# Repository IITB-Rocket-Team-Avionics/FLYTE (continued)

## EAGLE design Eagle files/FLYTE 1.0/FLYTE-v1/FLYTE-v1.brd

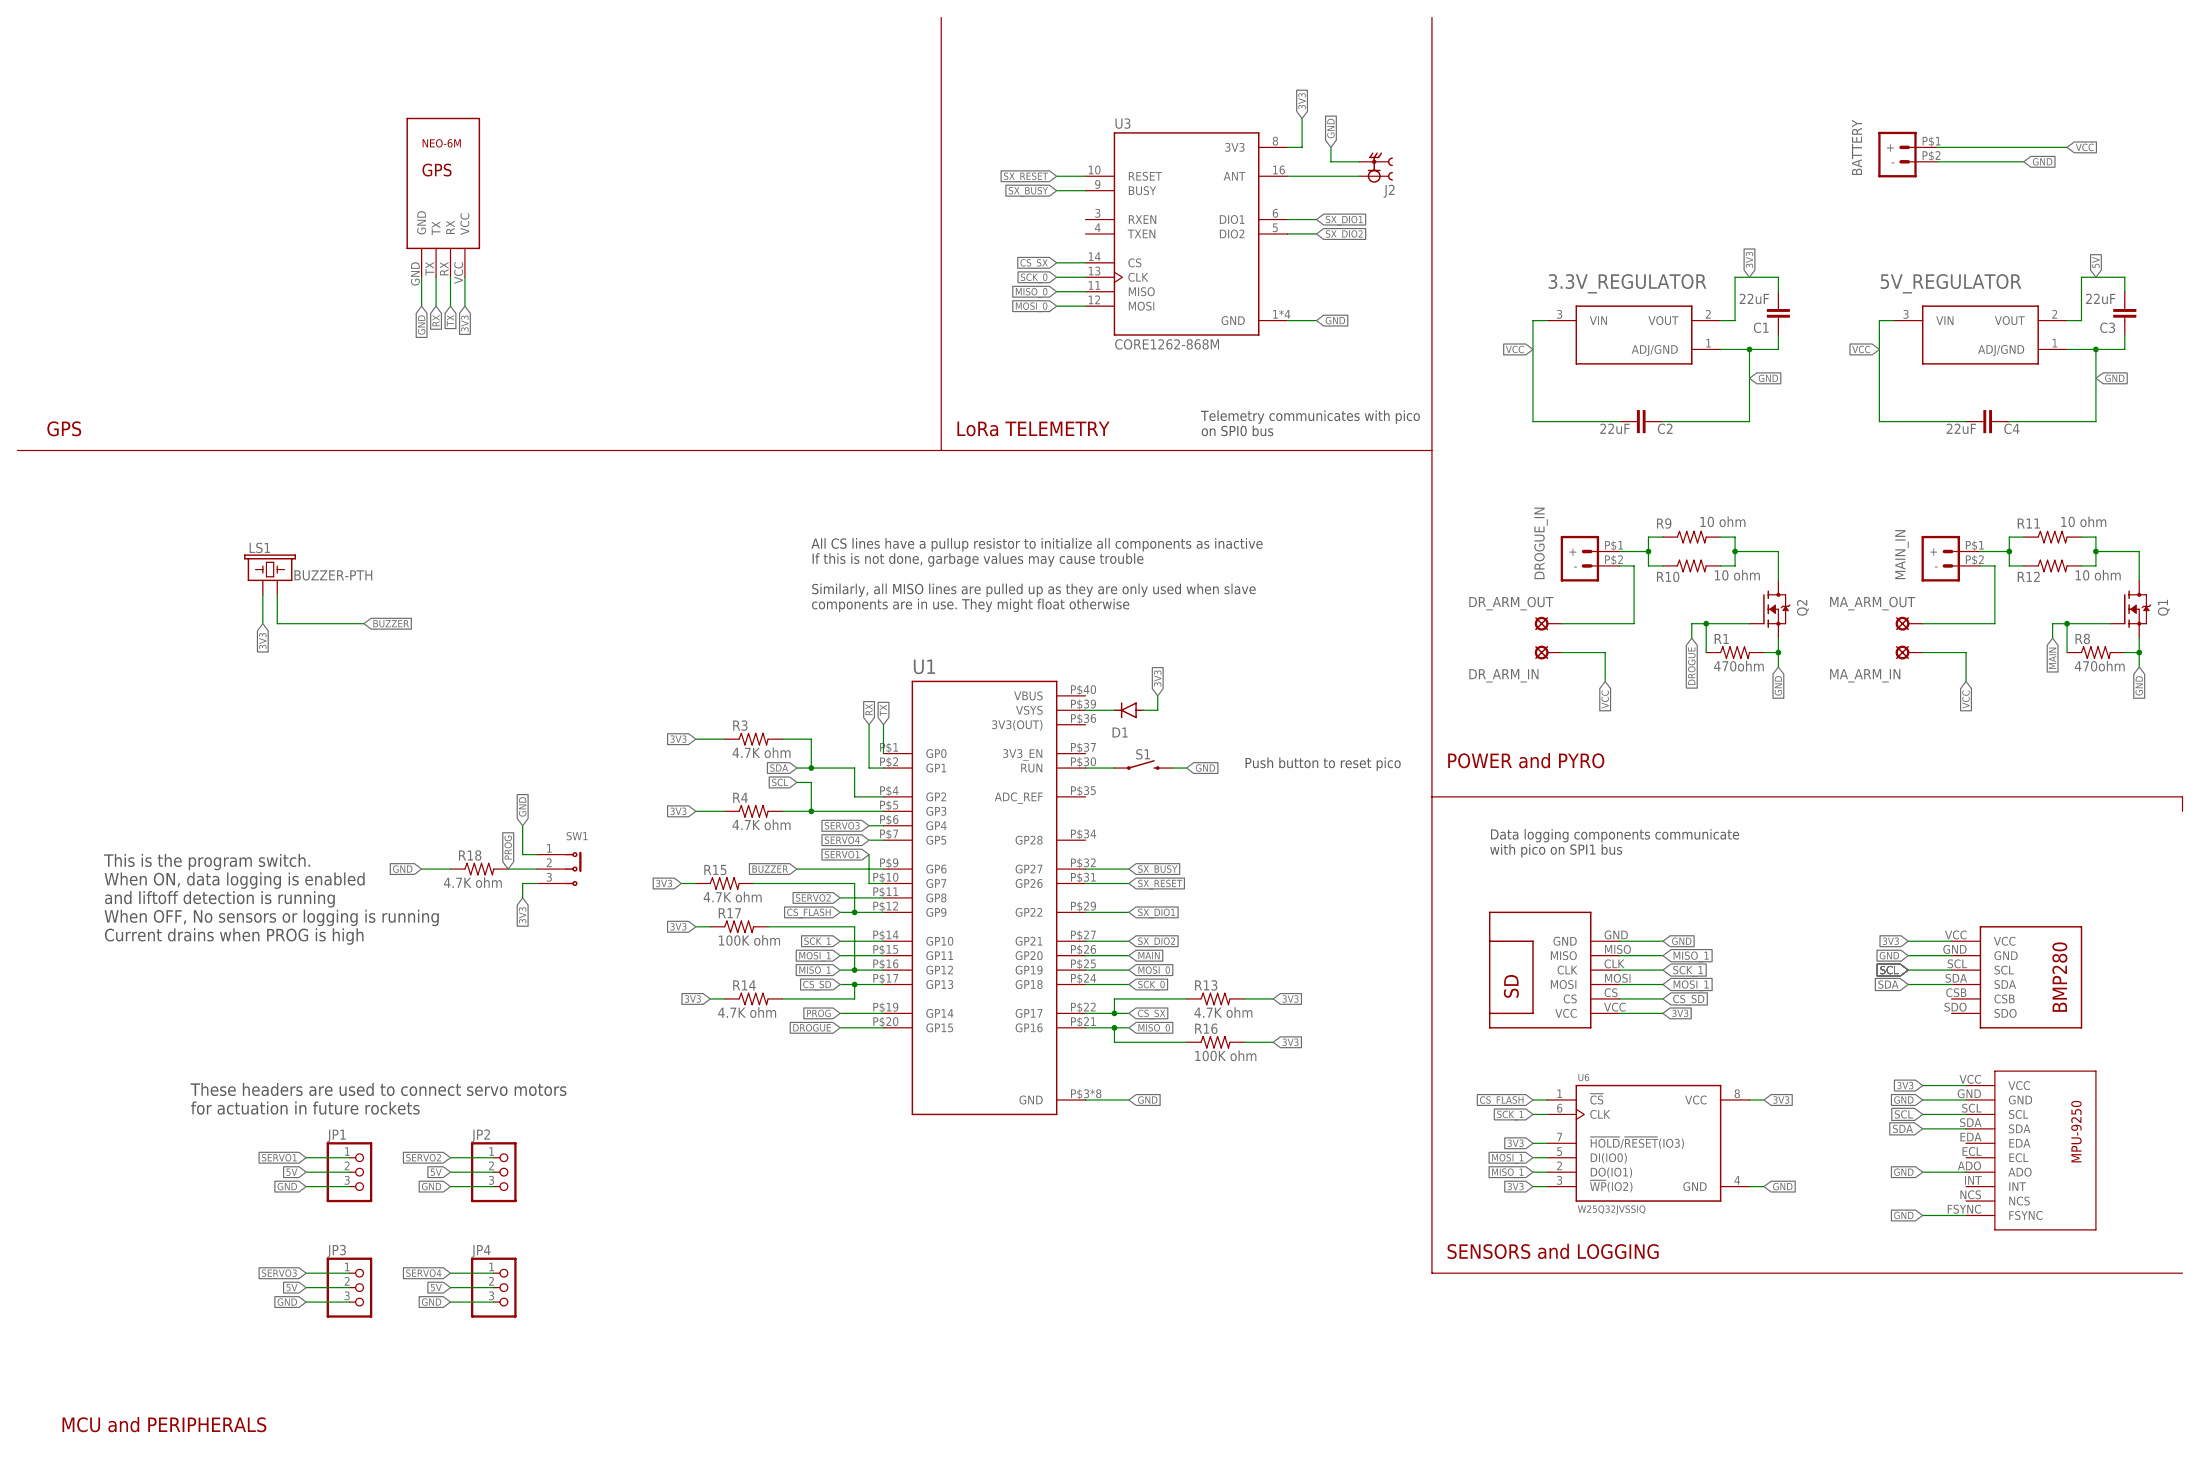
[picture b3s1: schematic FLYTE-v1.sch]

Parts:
3.3V_REGULATOR, 5V_REGULATOR: AMS1117-3.3; SOT229P700X180-4N
BATTERY: XT30UPB-M
C1, C2, C3, C4: 22uF; 0805
D1: 1N4004; DO41-10
DROGUE_IN: XT30UPB-M
DR_ARM_IN: LSP10
DR_ARM_OUT: LSP10
J2: CONSMA002; LINX_CONSMA002
JP1, JP2, JP3, JP4: PINHD-1X3; 1X03
LS1: BUZZER-PTH; BUZZER-12MM
MAIN_IN: XT30UPB-M
MA_ARM_IN: LSP10
MA_ARM_OUT: LSP10
Q1, Q2: IRF540NPBF; TO254P1054X469X1930-3
R1, R8: 470ohm; R0805
R3, R4, R13, R14, R15, R18: 4.7K ohm; R0805
R9, R10, R11, R12: 10 ohm; 0207/10
R16, R17: 100K ohm; R0805
S1: MOMENTARY-SWITCH-SPST-PTH-6.0MM; TACTILE_SWITCH_PTH_6.0MM
SW1: 1825159-1; SW_1825159-1
U1: RASPBERRY_PICO-NO_DEBUG; PICO-PKG-NO_DEBUG
U3: CORE1262-868M; XCVR_CORE1262-868M
U6: W25Q32JVSSIQ; SOIC127P790X216-8N
U$1: BMP280
U$2: GY-9250
U$3: SDREADER
U$4: NEO-6M

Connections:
3V3: 3.3V_REGULATOR.2 (VOUT), C1.2, D1.A, LS1.+ (1), R3.1, R4.1, R13.2, R14.1, R15.1, R16.2, R17.1, SW1.3, U3.8 (3V3), U6.3 (!WP!(IO2)), U6.7 (!HOLD!/!RESET!(IO3)), U6.8 (VCC), U$1.VCC, U$2.VCC, U$3.VCC, U$4.VCC
3V3(OUT): U1.P$36 (3V3(OUT))
5V: 5V_REGULATOR.2 (VOUT), C3.2, JP1.2, JP2.2, JP3.2, JP4.2
ANT: J2.1, U3.16 (ANT)
BUZZER: LS1.- (2), U1.P$9 (GP6)
CS_FLASH: R15.2, U1.P$12 (GP9), U6.1 (!CS)
CS_SD: R14.2, U1.P$17 (GP13), U$3.CS
CS_SX: R13.1, U1.P$22 (GP17), U3.14 (CS)
DROGUE: Q2.1 (G), R1.1, U1.P$20 (GP15)
GND: 3.3V_REGULATOR.1 (ADJ/GND), 5V_REGULATOR.1 (ADJ/GND), BATTERY.P$2 (-), C1.1, C2.1, C3.1, C4.1, J2.S1 (2), J2.S2 (2), J2.S3 (2), J2.S4 (2), JP1.3, JP2.3, JP3.3, JP4.3, Q1.3 (S), Q2.3 (S), R1.2, R8.2, R18.1, S1.3 (2), SW1.1, U1.P$3 (GND), U1.P$8 (GND), U1.P$13 (GND), U1.P$18 (GND), U1.P$23 (GND), U1.P$28 (GND), U1.P$33 (GND), U1.P$38 (GND), U3.1 (GND), U3.2 (GND), U3.7 (GND), U3.15 (GND), U6.4 (GND), U$1.GND, U$2.ADO, U$2.FSYNC, U$2.GND, U$3.GND, U$4.GND
MAIN: Q1.1 (G), R8.1, U1.P$26 (GP20)
MISO_0: R16.1, U1.P$21 (GP16), U3.11 (MISO)
MISO_1: R17.2, U1.P$16 (GP12), U6.2 (DO(IO1)), U$3.MISO
MOSI_0: U1.P$25 (GP19), U3.12 (MOSI)
MOSI_1: U1.P$15 (GP11), U6.5 (DI(IO0)), U$3.MOSI
unnamed: D1.C, U1.P$39 (VSYS)
unnamed: DROGUE_IN.P$2 (-), DR_ARM_OUT.MP
unnamed: MAIN_IN.P$1 (+), R11.1, R12.1
unnamed: DROGUE_IN.P$1 (+), R9.1, R10.1
unnamed: S1.1, U1.P$30 (RUN)
unnamed: Q2.2 (D), R9.2, R10.2
unnamed: Q1.2 (D), R11.2, R12.2
unnamed: MAIN_IN.P$2 (-), MA_ARM_OUT.MP
PROG: R18.2, SW1.2, U1.P$19 (GP14)
RX: U1.P$2 (GP1), U$4.TX
SCK_0: U1.P$24 (GP18), U3.13 (CLK)
SCK_1: U1.P$14 (GP10), U6.6 (CLK), U$3.CLK
SCL: R4.2, U1.P$5 (GP3), U$1.SCL, U$2.SCL
SDA: R3.2, U1.P$4 (GP2), U$1.SDA, U$2.SDA
SERVO1: JP1.1, U1.P$10 (GP7)
SERVO2: JP2.1, U1.P$11 (GP8)
SERVO3: JP3.1, U1.P$6 (GP4)
SERVO4: JP4.1, U1.P$7 (GP5)
SX_BUSY: U1.P$32 (GP27), U3.9 (BUSY)
SX_DIO1: U1.P$29 (GP22), U3.6 (DIO1)
SX_DIO2: U1.P$27 (GP21), U3.5 (DIO2)
SX_RESET: U1.P$31 (GP26), U3.10 (RESET)
TX: U1.P$1 (GP0), U$4.RX
VBUS: U1.P$40 (VBUS)
VCC: 3.3V_REGULATOR.3 (VIN), 5V_REGULATOR.3 (VIN), BATTERY.P$1 (+), C2.2, C4.2, DR_ARM_IN.MP, MA_ARM_IN.MP

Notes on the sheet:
POWER and PYRO
LoRa TELEMETRY
GPS
SENSORS and LOGGING
This is the program switch. When ON, data logging is enabled and liftoff detection is running When OFF, No sensors or logging is running Current drains when PROG is high
Telemetry communicates with pico on SPI0 bus
Data logging components communicate with pico on SPI1 bus
All CS lines have a pullup resistor to initialize all components as inactive If this is not done, garbage values may cause trouble Similarly, all MISO lines are pulled up as they are only used when slave components are in use. They might float otherwise
Push button to reset pico
These headers are used to connect servo motors for actuation in future rockets
MCU and PERIPHERALS

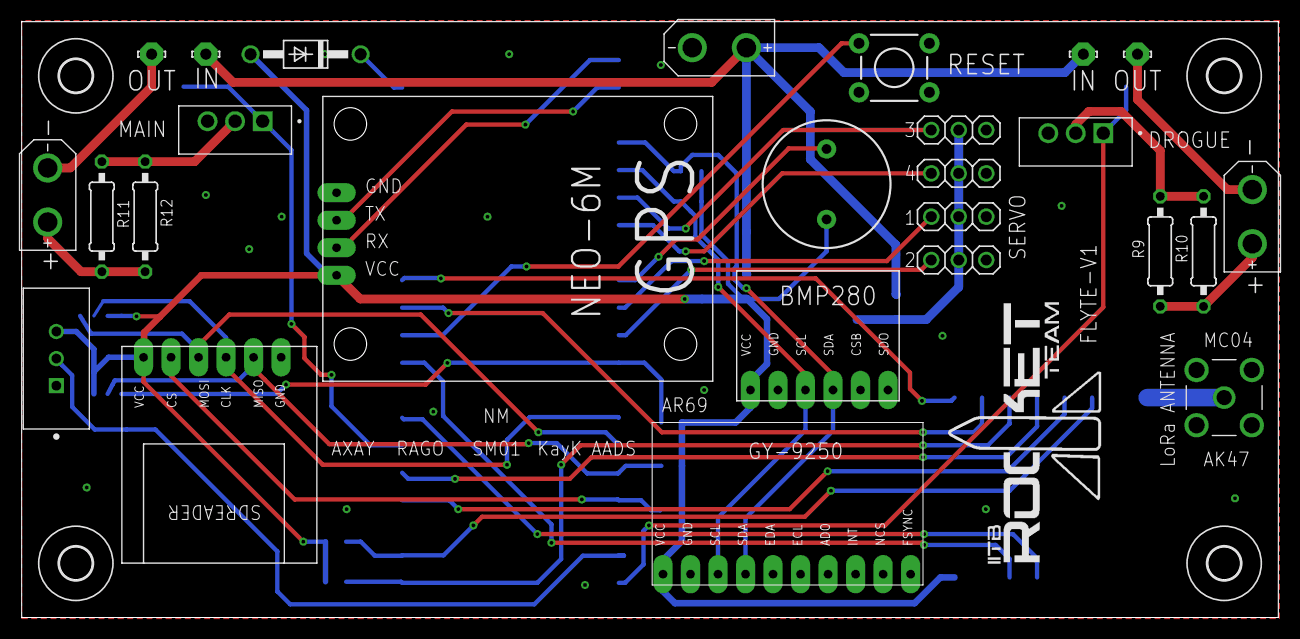
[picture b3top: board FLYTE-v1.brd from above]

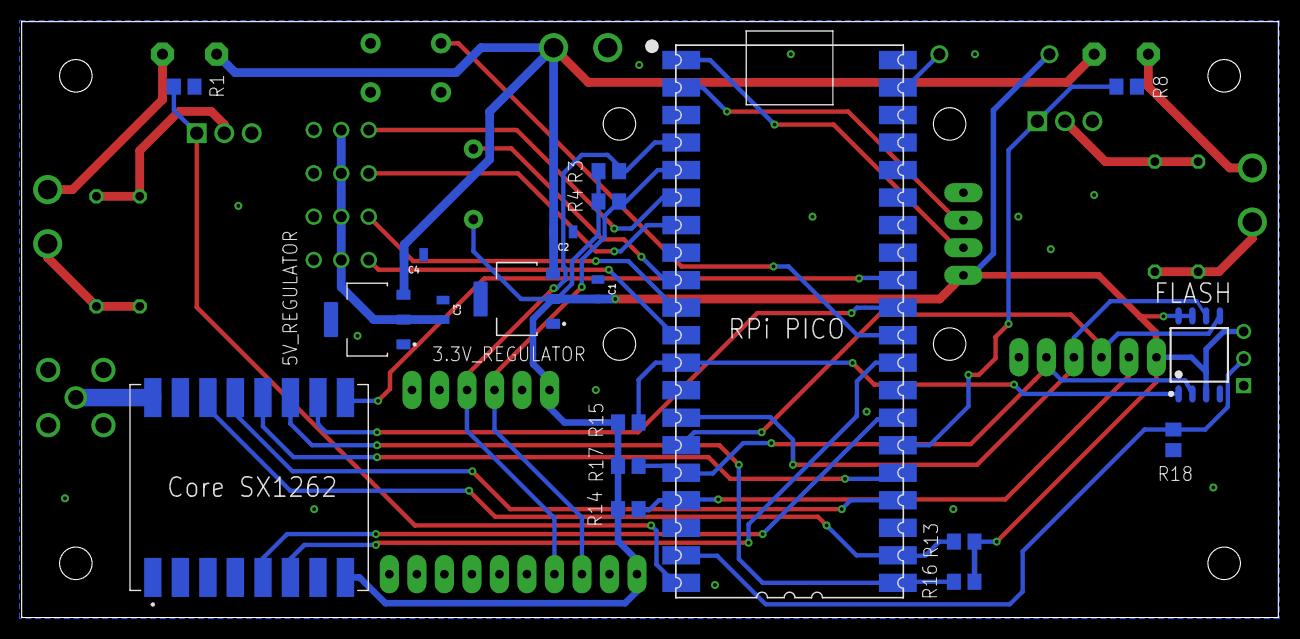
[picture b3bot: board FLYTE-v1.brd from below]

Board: 2 copper layers, 116.0 x 55.0 mm, 49 parts (19 on the bottom side), 38 nets.

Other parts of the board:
U$5, U$6, U$7, U$8: 3,0

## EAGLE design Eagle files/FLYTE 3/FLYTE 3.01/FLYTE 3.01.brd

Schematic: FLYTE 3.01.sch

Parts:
AC1: KX134-1211; KX1341211
BOOT: DTSM-3
BUZZER: BUZZER; CUI_CMT-8530S-SMT
C1, C4, C35, C38: CAPACITOR.0603; 0603
C2, C3: 24 pF; 0603
C5, C6, C7, C9, C11, C12, C13, C14, C15, C16, C19, C20, C21, C22, C25, C61: 100 nF; 0603
C8, C10, C26, C53, C55, C56, C59, C63, C115: 1 uF; 0603
C17, C29, C30, C31, C50, C51, C101: 0.1 uF; 0603
C18, C41, C43, C45, C47, C99, C100: 10uF; EIA3216-18/A-W
C23, C24: 25 pF; 0603
C27, C32: 10 nF; 0603
C28: 470 pF; 0603
C33, C37: 120 pF; 0603
C34: 47pF; 0603
C36: 1 nF; 0603
C39: 1uF; 0603
C40: 10uF; 0603
C42, C44, C46, C48, C49: 10 uF; EIA3216-18/A-W
C52, C58, C60: 100 uF; 1206
C54: 10 pF; 0603
C57, C62: 4.7 uF; 0603
CHIP_ANT: W3010; XCVR_W3010
D1, D2, D10, D13: RSX501LAM20TR; SODFL4725X105N
D4, D5, D6, D7, D11, D12: LED.0603; 0603.LED
FIN_1, FIN_2, FIN_3, FIN_4: 03-JST-B3B-XH-A; B3B-XH
FLASH: W25Q128JVSIQ; SOIC127P790X216-8N
GNSS: TESEO-LIV3F; SON110P970X1010X230-18N
H2, H3, H4: MOUNT-PAD-ROUND3.0; 3,0-PAD
IC1: BMP280
IC2: MPXV5100DP
IC3: AS179-92LF; SOT65P220X100-6N
IC6: MAX8574EUT+T; SOT95P280X145-6N
IC9: MCP73844-840I_MS; SOP65P490X110-8N
J1, J2, J3, J4, J5, J9, J13: 282834-2; TE_282834-2
J6: 503182-1852; 5031821852
J7: XT60-M; AMASS_XT60-M
J8: SMA_CONNECTOR; LPRS_SMA_CONNECTOR
J10, J11: B2B-XH-A(LF)(SN); JST_B2B-XH-A(LF)(SN)
L1: 33 uH; INDP125125X600N
L6: 27 nH; 0603
L7: 5.6 nH; 0603
L8: 22 uH; 0603
LED: LED.0603; 0603.LED
LNA: BGA725L6; AMP_BGA725L6E6327FTSA1
MOTOR: 03-JST-B3B-XH-A; B3B-XH
Q1: SI7625DN-T1-GE3; SIS862DNT1GE3
Q2, Q3, Q4, Q5: MOSFET-PWIDE; SOT23-WIDE
R0, R9, R10, R13, R15, R20, R21, R26, R36, R43, R70, R72, R73, R80, R81, R82, R83, R84, R85, R93, R94, R95, R96, R101: 10k ohm; 0603
R1, R5: 1k ohm; 0603
R2, R19, R58: 60 ohm; 0603
R3, R4: 27.4 ohm; 0603
R6, R7: 5.1k ohm; 0603
R8: 100 ohm; 0603
R11, R14: 10 kohm; 0603
R12, R18, R22, R28, R31, R33, R53, R55, R57, R61, R65, R66, R68, R71, R75, R77, R79, R87, R89, R91: 100k ohm; 0603
R16: 365k ohm; 0603
R17: 57.6k ohm; 0603
R23, R27, R30, R32, R35: 301k ohm; 0603
R24, R63: 0.1 ohm; 0603
R25, R37, R38, R39, R40, R41, R42, R44, R45, R46, R47, R48, R49, R50, R51, R52: 0.13 ohm; 0603
R29, R59: 315 ohm; 0603
R34, R64: 158 ohm; 0603
R54, R56, R60, R62, R67, R69, R74, R76, R78, R86, R88, R90, R92: 140k ohm; 0603
R97: RESISTOR.0603; 0603
R98, R99, R100: 0 ohm; 0603
R102: RESISTOR.0805; 0805
RP2040: RP2040-QFN56; RP2040-QFN-56
SAW: SAW_FILTER; FIL_AFS14A04-1575.42-T3
U1: BNO055; LGA28R50P4X10_380X520X100
U2, U3, U5, U7: CJ3400; SOT91P240X120-3N
U4, U10: LM1117-3.3; SOT230
U6, U9, U15, U16: ADS1115IDGSR; SOP50P490X110-10N
U8, U11, U12, U13, U14: MIC29302WU-TR; TO-263-5_MCH
U17: CP2102; QFN50P500X500X100-29N
U$1, U$3: SN74LVC1G04DBVR; SOT23-5
VR1: XL6009; DPAK170P1435X465-6N
X6: USB Type C; USB_C_CUSB31-CFM2AX-01-X
XBEE: XBP9B-XCST-021; DIP2200W51P200L3294H279Q20P
XTAL: ASE
Y1: FC-135_32.7680KA-A0; XTAL_FC-135_32.7680KA-A0

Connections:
1V1: C6.2, C7.2, C8.2, RP2040.23 (DVDD0), RP2040.45 (VREG_OUT), RP2040.50 (DVDD1)
3V3: C4.2, C34.2, C39.2, C40.2, J1.1, Q3.2 (S), R93.2, R94.2, U4.2 (VOUT), U4.4 (VOUT_2), XBEE.1 (VCC)
3V3_OP: AC1.1 (SDO/ADDR), AC1.3 (IO_VDD), AC1.7 (VDD), AC1.10 (NCS), C5.1, C9.2, C10.2, C11.2, C12.2, C13.2, C14.2, C15.2, C16.2, C19.2, C20.1, C21.1, C25.1, C30.2, C31.2, C32.2, C61.2, C115.2, FLASH.8 (VCC), IC1.6 (VDDIO), IC1.8 (VDD), J6.4 (VDD), L6.1, Q3.3 (D), R0.2, R10.2, R13.2, R14.1, R43.1, R72.2, R73.2, R80.2, R81.2, R82.2, R83.2, R84.2, R85.2, RP2040.1 (IOVDD0), RP2040.10 (IOVDD1), RP2040.22 (IOVDD2), RP2040.26 (RUN), RP2040.33 (IOVDD3), RP2040.42 (IOVDD4), RP2040.43 (ADC_AVDD), RP2040.44 (VREG_IN), RP2040.48 (USB_VDD), RP2040.49 (IOVDD5), U1.3 (VDD), U1.4 (NBOOT_LOAD_PIN), U1.28 (VDDIO), U16.7 (AIN3), U$1.1 (NC), U$1.5 (VCC)
3V3_SET: C62.1, J1.2, Q3.1 (G), R101.2, U17.6 (VDD)
5V: C17.1, C26.1, C27.1, C29.1, C38.2, C50.1, C51.1, IC2.2 (VS), MOTOR.P$2, U6.8 (VDD), U9.1 (ADDR), U9.8 (VDD), U10.2 (VOUT), U10.4 (VOUT_2), U15.8 (VDD), U16.8 (VDD)
BC: J9.2, Q4.1 (G), R70.2, U$3.2 (A)
BUZZER: BUZZER.P, RP2040.17 (GPIO14)
CAM: D12.P$1 (1), RP2040.11 (GPIO8), U14.1 (EN)
CC1: R7.1, X6.A5 (CC1)
CC2: R6.1, X6.B5 (CC2)
CSB: IC1.2 (CSB), R10.1
CS_SD: J6.2 (CD/DAT3), R43.2, RP2040.3 (GPIO1)
CTRL: D6.P$1 (1), RP2040.12 (GPIO9), U8.1 (EN), U11.1 (EN), U12.1 (EN), U13.1 (EN)
CTS: R98.1, XBEE.12 (NCTS/DIO7)
D1: FIN_1.P$2, R25.2, R37.2, R38.2, R39.2, R55.1
D2: FIN_2.P$2, R45.2, R46.2, R47.2, R48.2, R68.1
D3: FIN_3.P$2, R40.2, R41.2, R42.2, R44.2, R77.1
D4: FIN_4.P$2, R49.2, R50.2, R51.2, R52.2, R89.1
D+: R3.2, R102.1, X6.A6 (D+), X6.B6 (D+)
D+1: R102.2, U17.4 (D+)
D-: R4.2, U17.5 (D-), X6.A7 (D-), X6.B7 (D-)
DROGUE: R15.2, RP2040.32 (GPIO21), U5.1 (G)
DTR: R100.1, XBEE.9 (NDTR/SLEEP_RQ/DIO8)
FB: C54.1, IC6.1 (FB), R18.1, R20.1
FIN_1: FIN_1.P$3, RP2040.6 (GPIO4)
FIN_2: FIN_2.P$3, RP2040.7 (GPIO5)
FIN_3: FIN_3.P$3, RP2040.8 (GPIO6)
FIN_4: FIN_4.P$3, RP2040.9 (GPIO7)
GND: AC1.4 (TRIG), AC1.8 (GND_1), AC1.9 (GND_2), BOOT.1, C1.1, C2.1, C3.1, C4.1, C5.2, C6.1, C7.1, C8.1, C9.1, C10.1, C11.1, C12.1, C13.1, C14.1, C15.1, C16.1, C17.2, C18.-, C19.1, C20.2, C21.2, C22.1, C23.2, C24.2, C25.2, C26.2, C27.2, C28.1, C29.2, C30.1, C31.1, C32.1, C34.1, C35.1, C36.1, C38.1, C39.1, C40.1, C41.-, C42.-, C43.-, C44.-, C45.-, C46.-, C47.-, C48.-, C49.-, C50.2, C51.2, C52.1, C53.1, C55.2, C56.2, C57.2, C58.1, C59.1, C60.1, C61.1, C62.2, C63.2, C99.-, C100.-, C101.1, C115.1, CHIP_ANT.2 (GND), CHIP_ANT.3 (GND), FIN_1.P$1, FIN_2.P$1, FIN_3.P$1, FIN_4.P$1, FLASH.4 (GND), GNSS.1 (GND), GNSS.10 (GND_RF_1), GNSS.12 (GND_RF_2), H2.B3,0, H3.B3,0, H4.B3,0, IC1.1 (GND), IC1.7 (GND), IC2.3 (GND), IC3.2 (GND), IC6.2 (GND), IC9.6 (VSS), J6.6 (VSS), J6.9 (VSS), J6.10 (VSS), J6.11 (VSS), J6.12 (VSS), J6.13 (VSS), J6.14 (VSS), J6.15 (VSS), J7.N (NEG), J8.G1 (2), J8.G2 (2), J8.G3 (2), J8.G4 (2), J9.1, J10.1, J11.1, LNA.1 (GND), LNA.4 (GNDRF), MOTOR.P$1, R2.2, R6.2, R7.2, R8.2, R9.1, R11.1, R12.2, R15.1, R17.2, R19.2, R20.2, R21.1, R22.2, R26.1, R28.2, R29.1, R31.2, R33.2, R34.1, R36.1, R54.2, R56.2, R58.2, R59.2, R60.2, R62.2, R67.2, R69.2, R74.2, R76.2, R78.2, R86.2, R88.2, R90.2, R92.2, R95.1, R97.2, R101.1, RP2040.19 (TESTEN), RP2040.57 (GND), RP2040.58 (GND), RP2040.59 (GND), RP2040.60 (GND), RP2040.61 (GND), RP2040.62 (GND), RP2040.63 (GND), RP2040.64 (GND), RP2040.65 (GND), RP2040.66 (GND), SAW.B (GND), SAW.D (GND), SAW.E (GND), U1.2 (GND), U1.5 (PS1), U1.6 (PS0), U1.10 (PIN10), U1.15 (PIN15), U1.16 (PIN16), U1.18 (COM2), U1.25 (GNDIO), U2.2 (S), U3.2 (S), U4.1 (ADJ/GND), U5.2 (S), U6.1 (ADDR), U6.3 (GND), U7.2 (S), U8.3 (GND), U8.6, U9.3 (GND), U10.1 (ADJ/GND), U11.3 (GND), U11.6, U12.3 (GND), U12.6, U13.3 (GND), U13.6, U14.3 (GND), U14.6, U15.3 (GND), U16.3 (GND), U17.3 (GND), U17.29 (GND), U17.P$1 (GND), U$1.3 (GND), U$3.3 (GND), VR1.1 (GND), X6.A1B12 (GND), X6.B1A12 (GND), XBEE.10 (GND), XTAL.2 (GND), XTAL.4 (VDD)
GPS_RX: GNSS.3 (RX), R81.1, RP2040.15 (GPIO12)
GPS_TX: GNSS.2 (TX), R82.1, RP2040.16 (GPIO13)
IGN1: R36.2, RP2040.29 (GPIO18), U3.1 (G)
IGN2: R26.2, RP2040.30 (GPIO19), U2.1 (G)
LED: LED.P$1 (1), RP2040.18 (GPIO15)
MAIN: R21.2, RP2040.31 (GPIO20), U7.1 (G)
MISO: J6.7 (DAT0), R84.1, RP2040.2 (GPIO0)
MOS: D4.P$1 (1), D13.2 (A), J13.2, Q1.5 (D_1), Q1.6 (D_2), Q1.7 (D_3), Q1.8 (D_4), Q1.9 (D_5), Q1.10 (D_6), Q1.11 (D_7)
MOSI: J6.3 (CMD), R85.1, RP2040.5 (GPIO3)
unnamed: D1.2 (A), IC6.4 (LX), L8.2
unnamed: LED.P$2 (2), R2.1
unnamed: C3.2, R5.1, XTAL.1 (TRI)
unnamed: C33.1, GNSS.11 (RF_IN)
unnamed: R12.1, R27.2, U8.5 (ADJ)
unnamed: BUZZER.N, R8.1
unnamed: D12.P$2 (2), R19.1
unnamed: J6.1 (DATA2), R13.1
unnamed: GNSS.6 (VBATT), GNSS.7 (VCC_IO), GNSS.8 (VCC), L6.2
unnamed: C22.2, U1.9 (CAP)
unnamed: R11.2, U1.17 (COM3)
unnamed: J6.8 (DAT1), R72.1
unnamed: R28.1, R30.2, U11.5 (ADJ)
unnamed: R31.1, R32.2, U12.5 (ADJ)
unnamed: R14.2, U1.11 (NRESET)
unnamed: R22.1, R23.2, U14.5 (ADJ)
unnamed: R33.1, R35.2, U13.5 (ADJ)
unnamed: D10.2 (A), L1.1, VR1.3 (SW), VR1.6 (SW)
unnamed: R16.2, R17.1, VR1.5 (FB)
unnamed: R55.2, R56.1, U6.5 (AIN1)
unnamed: R53.2, R54.1, U6.4 (AIN0)
unnamed: L7.1, LNA.5 (AI)
unnamed: C37.1, L7.2
unnamed: C33.2, SAW.A (OUT)
unnamed: LNA.3 (AO), SAW.C (IN)
unnamed: C37.2, IC3.5 (J1)
unnamed: CHIP_ANT.1 (FEEDING), IC3.1 (J3)
unnamed: IC3.3 (J2), J8.1
unnamed: R57.2, R60.1, U6.6 (AIN2)
unnamed: R61.2, R62.1, U6.7 (AIN3)
unnamed: R66.2, R67.1, U9.4 (AIN0)
unnamed: R68.2, R69.1, U9.5 (AIN1)
unnamed: R71.2, R74.1, U9.6 (AIN2)
unnamed: R75.2, R76.1, U15.4 (AIN0)
unnamed: R77.2, R78.1, U15.5 (AIN1)
unnamed: R79.2, R86.1, U15.6 (AIN2)
unnamed: R87.2, R88.1, U16.4 (AIN0)
unnamed: R89.2, R90.1, U16.5 (AIN1)
unnamed: R91.2, R92.1, U16.6 (AIN2)
unnamed: R96.2, U17.9 (!RST)
unnamed: R97.1, U17.11 (!SUSPEND)
unnamed: R98.2, U17.23 (CTS)
unnamed: R99.2, U17.24 (RTS)
unnamed: IC9.1 (SENSE), Q2.2 (S), R24.1, R63.2
unnamed: R100.2, U17.28 (DTR)
unnamed: C57.1, IC6.5 (SW), L8.1
unnamed: C54.2, C55.1, D1.1 (K), Q1.4 (G), R18.2
unnamed: D4.P$2 (2), R29.2
unnamed: D5.P$2 (2), R34.2
unnamed: D6.P$2 (2), R58.1
unnamed: D7.P$2 (2), R59.1
unnamed: D11.P$2 (2), R64.1
unnamed: IC9.3 (STAT1), R64.2
unnamed: IC9.4 (EN), R65.1
unnamed: IC9.8 (DRV), Q2.1 (G)
unnamed: C101.2, IC9.5 (TIMER)
unnamed: Q5.1 (G), U$3.4 (Y)
N_S: IC3.6 (V2), U$1.4 (Y)
PYRO_DROGUE: J3.2, R71.1, U5.3 (D)
PYRO_IGN1: J4.2, R79.1, U3.3 (D)
PYRO_IGN2: J5.2, R91.1, U2.3 (D)
PYRO_MAIN: J2.2, R57.1, U7.3 (D)
QSPI_SCLK: FLASH.6 (CLK), RP2040.52 (QSPI_SCLK)
QSPI_SD0: FLASH.5 (DI(IO0)), RP2040.53 (QSPI_SD0)
QSPI_SD1: FLASH.2 (DO(IO1)), RP2040.55 (QSPI_SD1)
QSPI_SD2: FLASH.3 (/WP(IO2)), RP2040.54 (QSPI_SD2)
QSPI_SD3: FLASH.7 (/HOLD/RESET(IO3)), RP2040.51 (QSPI_SD3)
QSPI_SS: FLASH.1 (/CS), R0.1, R1.2, RP2040.56 (QSPI_SS)
RSSI: RP2040.35 (GPIO23), XBEE.6 (DIO10/PWM0)
RTS: R99.1, XBEE.16 (NRTS/DIO6)
S: IC3.4 (V1), RP2040.27 (GPIO16), U$1.2 (A)
SCK: J6.5 (CLK), R83.1, RP2040.4 (GPIO2)
SCL: AC1.12 (SCLK/SCL), IC1.4 (SCK), R73.1, RP2040.14 (GPIO11), U1.19 (COM1), U6.10 (SCL), U9.10 (SCL), U15.1 (ADDR), U15.10 (SCL), U16.10 (SCL)
SDA: AC1.2 (SDI/SDA), IC1.3 (SDI), R80.1, RP2040.13 (GPIO10), U1.20 (COM0), U6.9 (SDA), U9.9 (SDA), U15.9 (SDA), U16.1 (ADDR), U16.9 (SDA)
SDO: IC1.5 (SDO), R9.2
TEL_RST: RP2040.34 (GPIO22), XBEE.5 (!RESET)
TEL_RX: R93.1, RP2040.36 (GPIO24), U17.26 (TXD), XBEE.3 (DIN/NCONFIG/DIO14)
TEL_TX: R94.1, RP2040.37 (GPIO25), U17.25 (RXD), XBEE.2 (DOUT/DIO13)
USB+: C56.1, IC6.3 (!SHDN), IC6.6 (VCC), Q4.2 (S), Q5.2 (S), R70.1, U$3.1 (NC), U$3.5 (VCC), X6.A4B9 (VBUS), X6.B4A9 (VBUS)
USB_BOOT: BOOT.2, R1.1
USB_BST: C58.2, C59.2, C60.2, C99.+, D10.1 (K), D11.P$1 (1), IC9.2 (VDD), R16.1, R24.2, R63.1, R65.2
USB_CHG: C52.2, C53.2, L1.2, Q4.3 (D), R95.2, VR1.2 (EN), VR1.4 (VIN)
USB_DM: R4.1, RP2040.46 (USB_DM)
USB_DP: R3.1, RP2040.47 (USB_DP)
VBUS: C63.1, D2.2 (A), D5.P$1 (1), Q5.3 (D), R96.1, U17.7 (REGIN), U17.8 (VBUS)
VCC: C1.2, C18.+, C35.2, D2.1 (K), D13.1 (K), U4.3 (VIN), U10.3 (VIN), U14.2 (IN)
VCC_PYRO: D7.P$1 (1), J2.1, J3.1, J4.1, J5.1, J13.1
VCC_RF: C36.2, GNSS.14 (VCC_RF), LNA.2 (VCC), LNA.6 (PON)
VOLT_DP: C28.2, IC2.4 (VOUT), U9.7 (AIN3)
VOLT_MOTOR: MOTOR.P$3, U15.7 (AIN3)
V_CAM: C49.+, J10.2, J11.2, R23.1, U14.4 (OUT)
V_FIN_1: C42.+, R25.1, R27.1, R37.1, R38.1, R39.1, R53.1, U8.4 (OUT)
V_FIN_2: C44.+, R30.1, R45.1, R46.1, R47.1, R48.1, R66.1, U11.4 (OUT)
V_FIN_3: C46.+, R32.1, R40.1, R41.1, R42.1, R44.1, R75.1, U12.4 (OUT)
V_FIN_4: C48.+, R35.1, R49.1, R50.1, R51.1, R52.1, R87.1, U13.4 (OUT)
XIN: C2.2, RP2040.20 (XIN), XTAL.3 (OUT)
XIN32: C23.1, U1.27 (XIN32), Y1.1
XOUT: R5.2, RP2040.21 (XOUT)
XOUT32: C24.1, U1.26 (XOUT32), Y1.2
XT60+: C41.+, C43.+, C45.+, C47.+, C100.+, IC9.7 (VBAT), J7.P (POS), Q1.1 (S_1), Q1.2 (S_2), Q1.3 (S_3), Q2.3 (D), R61.1, U8.2 (IN), U11.2 (IN), U12.2 (IN), U13.2 (IN)

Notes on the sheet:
FLASH
USB
RP2040
CRYSTAL OSCILLATOR
VBUS : Power from USB D+ : Data line 1 D- : Data line 2 CC1 & CC2 : Not sure what they are for but both must be pulled to GND using 5.1k ohm resistors when using Type-C USB SHLD : Outer covering of female USB connector. Should be grounded GND : Ground Try to route D+ and D- so that the differential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
Power C9-C16 : Decoupling capacitors for RP2040. Must be placed close to the power pins. C8 must be close to Pin 45, C10 must be close to Pin 44, rest can be jumbled around as you may like. There is one decoupling capacitor less than number of power pins. Not sure why, that's just how it is in the 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
Power C5 - Decoupling capacitor for flash. Must pe placed close to the flash. Boot When CS is pulled LOW on startup by pressing the button, the flash boots up as a mass storage device (like an SD Card). This is similar to plugging in a USB cable into a Pico while holding the BOOTSEL button. As a pr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
Purchase Links LED : https://evelta.com/green-led-smd-0603-package/ Buzzer : https://www.sunrom.com/p/electromagnetic-passive-buzzer-3-5v-smd-pcb-mount-mlt-8530
Crystal oscillators need a load capacitance to osciallte at the right frequency. This particular chip needs 12 pF. So, 2 capacitors of 22 pF each are placed to give an equivalent load capacitance of 11 pF. 24 pF capacitors were not available, but these get the job done. 1k ohm resistor to ensure th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
TESEO-LIV3F : GNSS Chip TX & RX : For UART communication SCL & SDA : For I2C communication PPS : Time pulse from GNSS VCC_RF : Power output from chip to active antenna C20 & C22 : Blocks DC voltage C18 & C21 : Decoupling capacitors GNSS_SWITCH : Used to switch between 3 antennae V1 : 0, V2 : 0 - RF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
GNSS
Telemetry communicates with pico on SPI0 bus

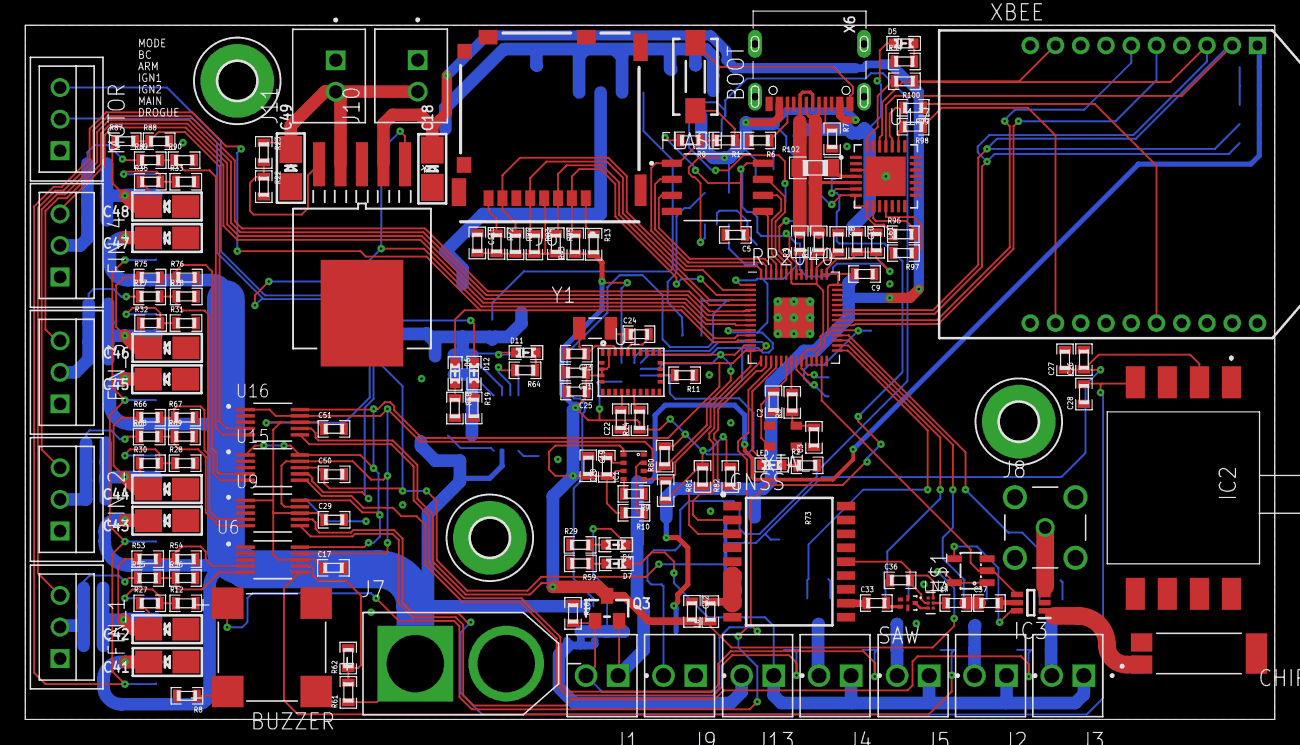
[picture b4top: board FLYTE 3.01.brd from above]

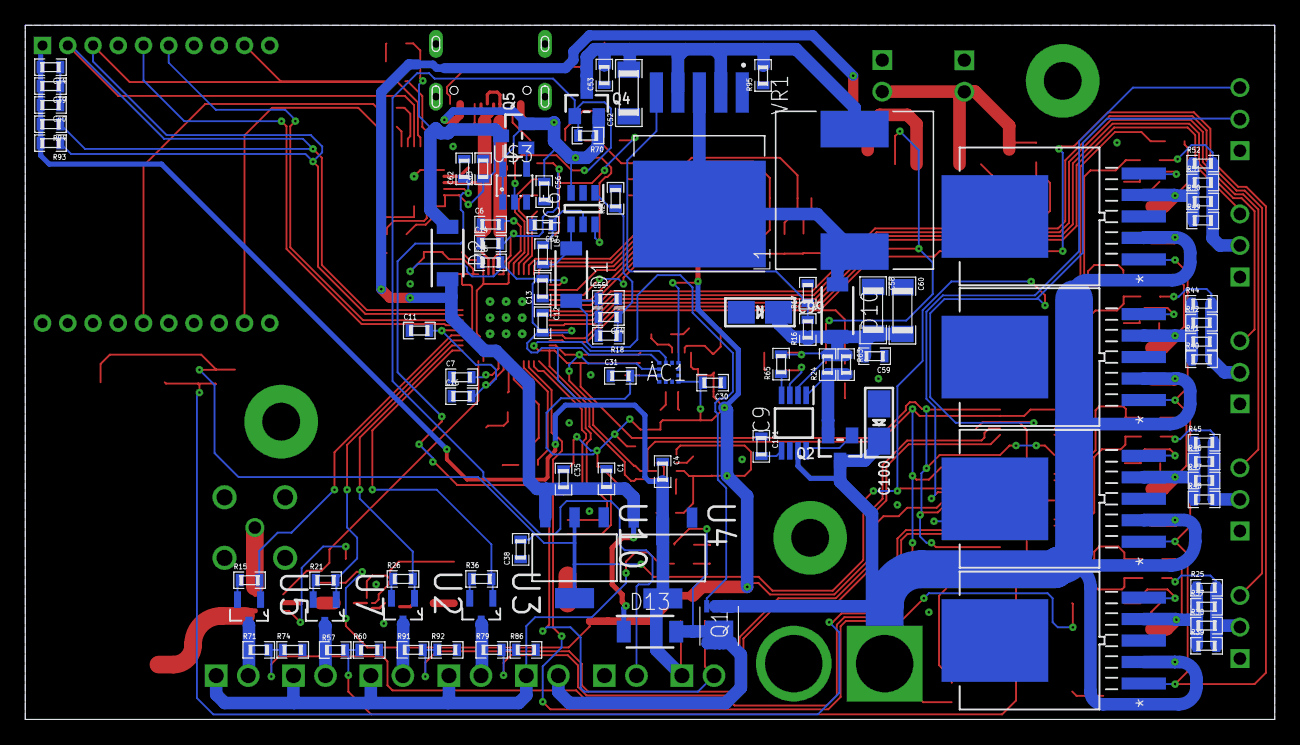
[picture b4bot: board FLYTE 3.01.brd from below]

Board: 2 copper layers, 99.0 x 55.0 mm, 248 parts (95 on the bottom side), 138 nets.

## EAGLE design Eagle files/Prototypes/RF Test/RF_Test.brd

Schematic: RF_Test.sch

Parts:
<-D: B5819WS; SOD2512X116N
AP2112: AP2112K-3.3TRG1; SOT95P282X130-5N
C1, C4, C5, C6: 100 nF; CAPC1608X90
C2, C3, C10: 22 pF; CAPC1608X90
C7, C12: 3.3 pF; CAPC1608X90
C8, C15, C16: 47 pF; CAPC1608X90
C9, C11: 8.2 pF; CAPC1608X90
C13: 1.5 pF; CAPC1608X90
C14, C18: 10 nF; CAPC1608X90
C17, C21: 1 nF; CAPC1608X90
C19, C23: 1 uF; CAPC1608X90
C20, C22: 120 pF; CAPC1608X90
CHIP: LED.0603; 0603.LED
CHIP_ANT: W3010; XCVR_W3010
D->: B5819WS; SOD2512X116N
EXT: LED.0603; 0603.LED
GNSS: TESEO-LIV3F; SON110P970X1010X230-18N
GNSS_EXT: CON-SMA-EDGE-S; RFSOLUTIONS_CON-SMA-EDGE-S
GNSS_SWITCH: RF_SWITCH; BGS13SN8E6327XTSA1
L1: 10 nH; INDC1608X90N
L2: 2.7 nH; INDC1608X90N
L3, L4, L7: 5.6 nH; INDC1608X90N
L5: 33 nH; INDC1608X90N
L6: 27 nH; INDC1608X90N
LNA: BGA725L6; AMP_BGA725L6E6327FTSA1
PATCH: LED.0603; 0603.LED
PICO: RASPBERRY_PICO-NO_DEBUG; PICO-PKG-NO_DEBUG
R1: LED_PATCH; RESC1608X50N
R2: LED_CHIP; RESC1608X50N
R3: LED_EXT; RESC1608X50N
R14: 10k ohm; RESC1608X50N
S: RF_SWITCH; SW_BGS12P2L6E6327XTSA1
SAW: SAW_FILTER; FIL_AFS14A04-1575.42-T3
SX1272: SX1272IMLTRT; QFN65P600X600X100-29N
SX_ANT: CON-SMA-EDGE-S; RFSOLUTIONS_CON-SMA-EDGE-S
XTAL: ASE

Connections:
3V3: AP2112.5 (VOUT), C1.2, C4.2, C18.2, C23.1, D->.A, GNSS_SWITCH.1 (VDD), L6.1, S.4 (VDD), SX1272.1 (VBAT1), SX1272.15 (VBAT2)
3V3(OUT): PICO.P$36 (3V3(OUT))
ANT_OFF: GNSS.13 (ANT_OFF), LNA.6 (PON), R14.1
CS: PICO.P$7 (GP5), SX1272.20 (NSS)
DIO0: PICO.P$9 (GP6), SX1272.9 (DIO0)
DIO1: PICO.P$10 (GP7), SX1272.10 (DIO1/DCLK)
DIO2: PICO.P$11 (GP8), SX1272.11 (DIO2/DATA)
DIO3: PICO.P$29 (GP22), SX1272.12 (DIO3)
DIO4: PICO.P$31 (GP26), SX1272.13 (DIO4)
DIO5: PICO.P$32 (GP27), SX1272.14 (DIO5)
GND: AP2112.2 (GND), C1.1, C2.1, C3.1, C4.1, C5.1, C6.1, C7.2, C9.2, C11.2, C12.2, C14.2, C15.2, C17.1, C18.1, C19.2, C21.1, C23.2, CHIP_ANT.2 (GND), CHIP_ANT.3 (GND), GNSS.1 (GND), GNSS.10 (GND_RF_1), GNSS.12 (GND_RF_2), GNSS_EXT.G1 (2), GNSS_EXT.G2 (2), GNSS_EXT.G3 (2), GNSS_EXT.G4 (2), GNSS_SWITCH.8 (DGND), LNA.1 (GND), LNA.4 (GNDRF), PICO.P$3 (GND), PICO.P$8 (GND), PICO.P$13 (GND), PICO.P$18 (GND), PICO.P$23 (GND), PICO.P$28 (GND), PICO.P$33 (GND), PICO.P$38 (GND), R1.1, R2.1, R3.1, R14.2, S.2 (GND), SAW.B (GND), SAW.D (GND), SAW.E (GND), SX1272.16 (GND), SX1272.22 (GND), SX1272.26 (GND), SX1272.29 (GND), SX_ANT.G1 (2), SX_ANT.G2 (2), SX_ANT.G3 (2), SX_ANT.G4 (2), XTAL.2 (GND), XTAL.4 (VDD)
GPS_RX: GNSS.3 (RX), PICO.P$21 (GP16)
GPS_SCL: GNSS.17 (SCL), PICO.P$25 (GP19)
GPS_SDA: GNSS.16 (SDA), PICO.P$24 (GP18)
GPS_TX: GNSS.2 (TX), PICO.P$22 (GP17)
MISO: PICO.P$6 (GP4), SX1272.18 (MISO)
MOSI: PICO.P$5 (GP3), SX1272.19 (MOSI)
unnamed: C22.2, GNSS_SWITCH.6 (RFIN)
unnamed: PATCH.P$1 (1), PICO.P$17 (GP13)
unnamed: CHIP_ANT.1 (FEEDING), GNSS_SWITCH.5 (RF1)
unnamed: C5.2, SX1272.2 (VR_ANA)
unnamed: C6.2, SX1272.3 (VR_DIG)
unnamed: L1.1, SX1272.25 (RFI)
unnamed: C7.1, C8.2, L1.2
unnamed: C8.1, S.3 (RF1)
unnamed: L2.1, SX1272.27 (PA_BOOST)
unnamed: C9.1, C10.2, L2.2, L5.2
unnamed: C10.1, L3.1
unnamed: C11.1, C13.2, L3.2, L4.1
unnamed: C12.1, C13.1, L4.2, S.1 (RF2)
unnamed: C14.1, C15.1, L5.1, SX1272.28 (VR_PA)
unnamed: C16.2, S.5 (RFIN)
unnamed: C16.1, SX_ANT.1
unnamed: GNSS.6 (VBATT), GNSS.7 (VCC_IO), GNSS.8 (VCC), L6.2
unnamed: C20.2, SAW.A (OUT)
unnamed: L7.1, LNA.5 (AI)
unnamed: C22.1, L7.2
unnamed: LNA.3 (AO), SAW.C (IN)
unnamed: D->.K, PICO.P$39 (VSYS)
unnamed: <-D.A, PICO.P$40 (VBUS)
unnamed: GNSS_EXT.1, GNSS_SWITCH.4 (RF3)
unnamed: PATCH.P$2 (2), R1.2
unnamed: CHIP.P$1 (1), PICO.P$16 (GP12)
unnamed: CHIP.P$2 (2), R2.2
unnamed: EXT.P$1 (1), PICO.P$15 (GP11)
unnamed: EXT.P$2 (2), R3.2
PATCH: GNSS_SWITCH.7 (RF2)
PPS: GNSS.4 (1PPS), PICO.P$34 (GP28)
RF_IN: C20.1, GNSS.11 (RF_IN)
RXTX: C17.2, S.6 (CTRL), SX1272.23 (RXTX)
S1: GNSS_SWITCH.3 (V1), PICO.P$20 (GP15)
S2: GNSS_SWITCH.2 (V2), PICO.P$19 (GP14)
SCK: PICO.P$4 (GP2), SX1272.17 (SCK)
VBUS: <-D.K, AP2112.1 (VIN), AP2112.3 (EN), C19.1
VCC_RF: C21.2, GNSS.14 (VCC_RF), LNA.2 (VCC)
XIN: C2.2, SX1272.4 (XTA), XTAL.3 (OUT)
XOUT: C3.2, SX1272.5 (XTB), XTAL.1 (TRI)

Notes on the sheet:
TESEO-LIV3F : GNSS Chip TX & RX : For UART communication SCL & SDA : For I2C communication PPS : Time pulse from GNSS VCC_RF : Power output from chip to active antenna C20 & C22 : Blocks DC voltage C18 & C21 : Decoupling capacitors GNSS_SWITCH : Used to switch between 3 antennae V1 : 0, V2 : 0 - RF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
GNSS
AP2112K-3.3TRG1 : 3.3V regulator C19 & C23 : Decoupling capacitors for regulator (from datasheet). Must be placed close to the regulator Purchase Links 1 uF Capacitors : https://evelta.com/1-uf-25v-0603-smd-multi-layer-ceramic-capacitor-0603x105k250ct-walsin/ AP2112K-3.3TRG1 : https://robu.in/produ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
POWER
PICO
SX1272 : Radio Chip SCK, CS, MOSI, MISO : SPI communication lines XTA, XTB : Connect to external 32 MHz crystal oscillator VBAT1, VBAT2, VR_ANA, VR_DIG : Power pins, only connect external power to VBAT1 & VBAT2 PA_BOOST : RF output in high-power mode VR_PA : Regulated power supply from chip while u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
SX1272

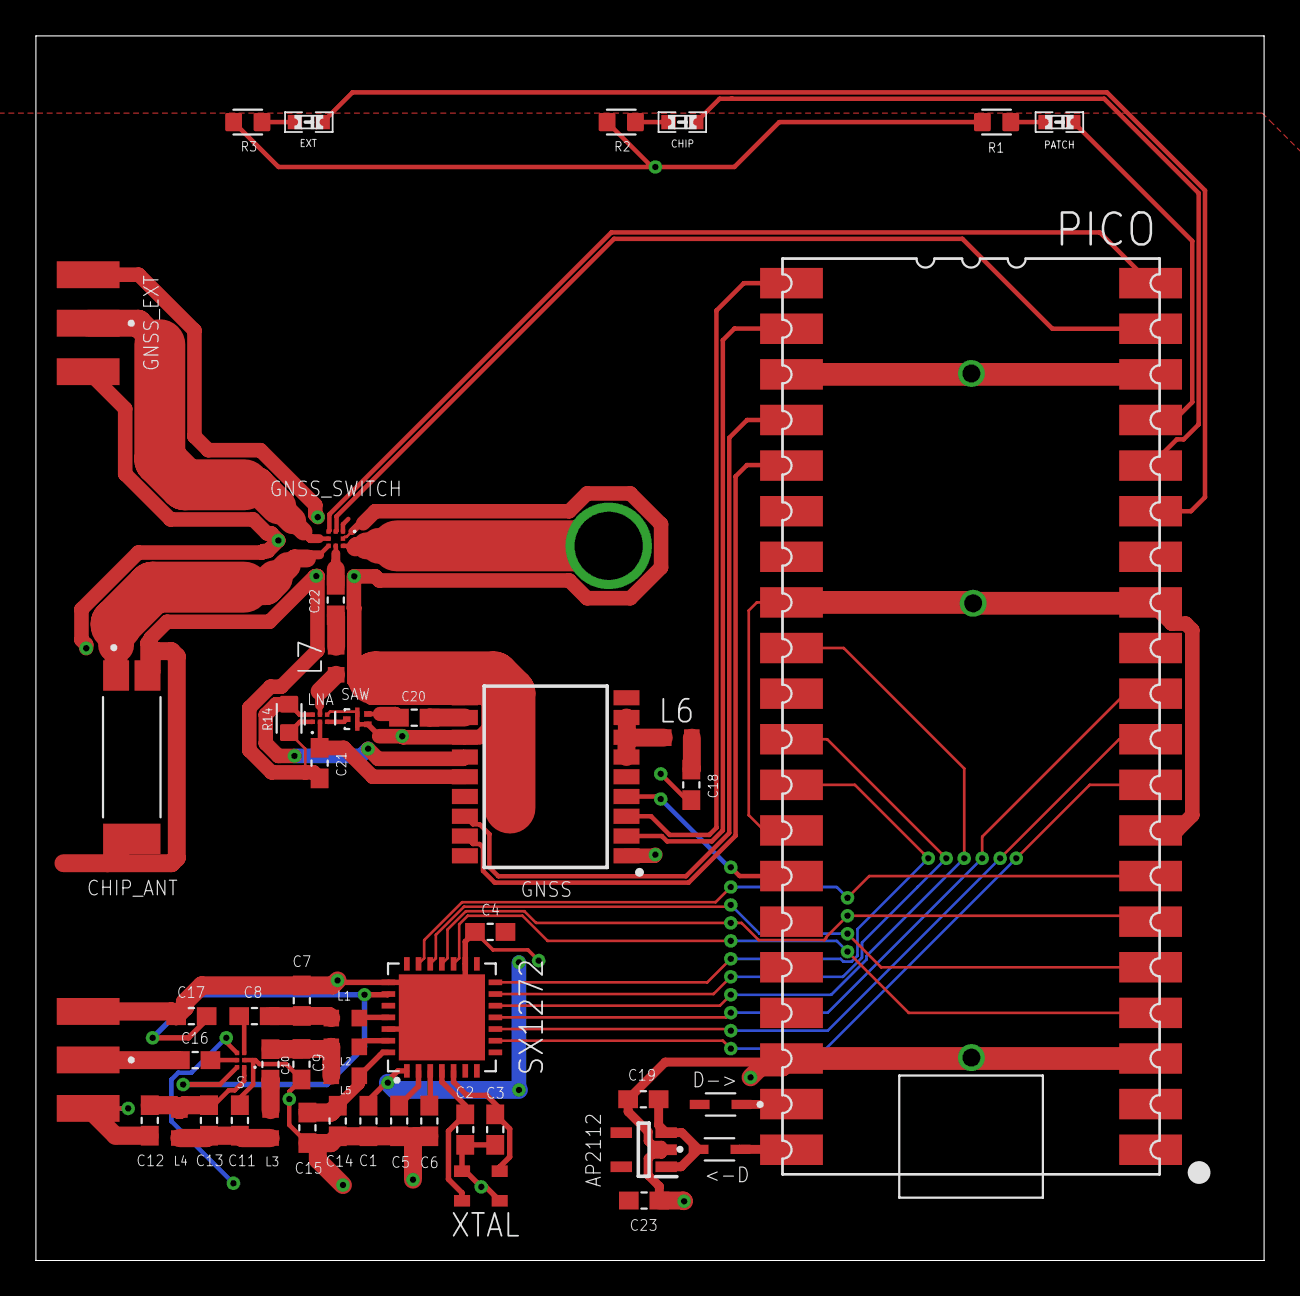
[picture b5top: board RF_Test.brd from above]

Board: 2 copper layers, 68.4 x 68.2 mm, 51 parts (0 on the bottom side), 55 nets.
